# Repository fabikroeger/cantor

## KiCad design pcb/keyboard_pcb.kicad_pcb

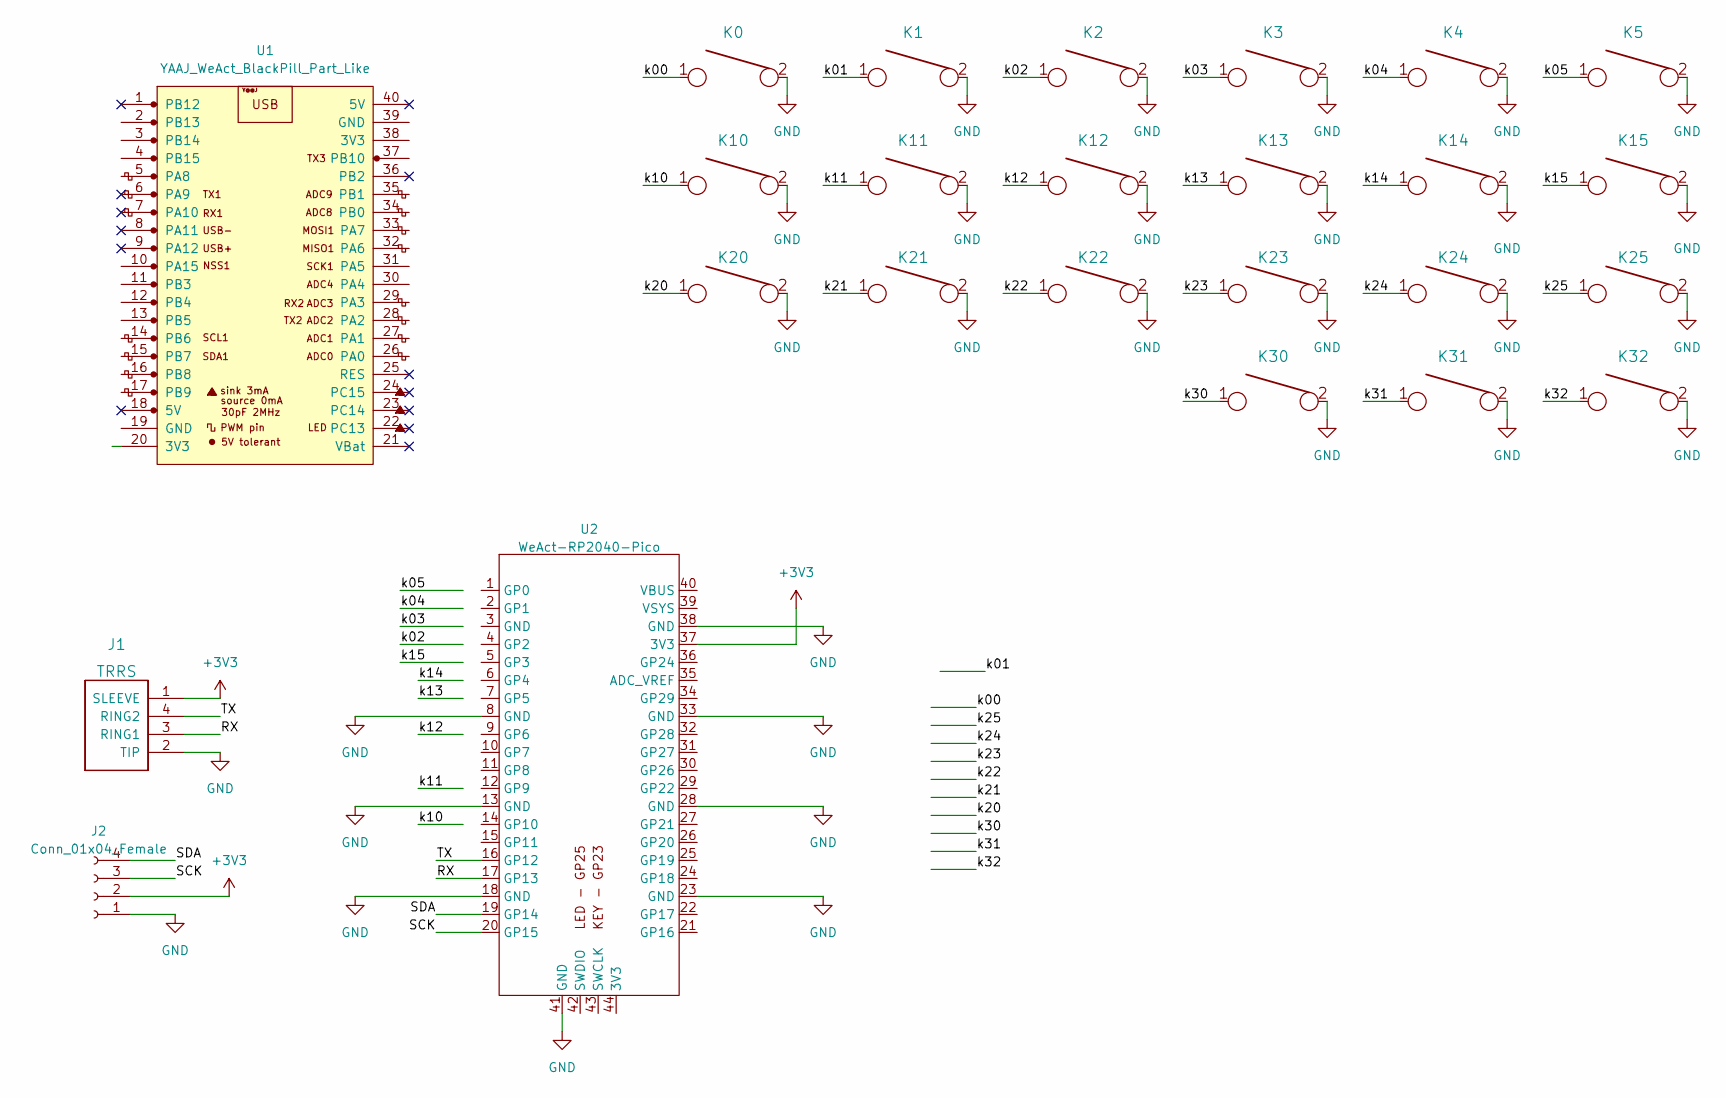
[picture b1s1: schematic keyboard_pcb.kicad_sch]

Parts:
J1: TRRS; TRRS-PJ-320A
J2: Conn_01x04_Female
K0, K1, K2, K3, K4, K5, K10, K11, K12, K13, K14, K15, K20, K21, K22, K23, K24, K25, K30, K31, K32: KEYSW; SW_PG1350_reversible
U1: YAAJ_WeAct_BlackPill_Part_Like; YAAJ_WeAct_BlackPill_2
U2: WeAct-RP2040-Pico

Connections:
+3V3: J1.1 (SLEEVE), J2.2, U2.37 (3V3)
/RX: J1.3 (RING1), U2.17 (GP13)
/SCK: J2.3, U2.20 (GP15)
/SDA: J2.4, U2.19 (GP14)
/TX: J1.4 (RING2), U2.16 (GP12)
/k00: K0.1
/k01: K1.1
/k02: K2.1
/k03: K3.1
/k04: K4.1
/k05: K5.1
/k10: K10.1
/k11: K11.1
/k12: K12.1
/k13: K13.1
/k14: K14.1
/k15: K15.1
/k20: K20.1
/k21: K21.1
/k22: K22.1
/k23: K23.1
/k24: K24.1
/k25: K25.1
/k30: K30.1
/k31: K31.1
/k32: K32.1
GND: J1.2 (TIP), J2.1, K0.2, K1.2, K2.2, K3.2, K4.2, K5.2, K10.2, K11.2, K12.2, K13.2, K14.2, K15.2, K20.2, K21.2, K22.2, K23.2, K24.2, K25.2, K30.2, K31.2, K32.2, U2.8 (GND), U2.13 (GND), U2.18 (GND), U2.23 (GND), U2.28 (GND), U2.33 (GND), U2.38 (GND), U2.41 (GND)

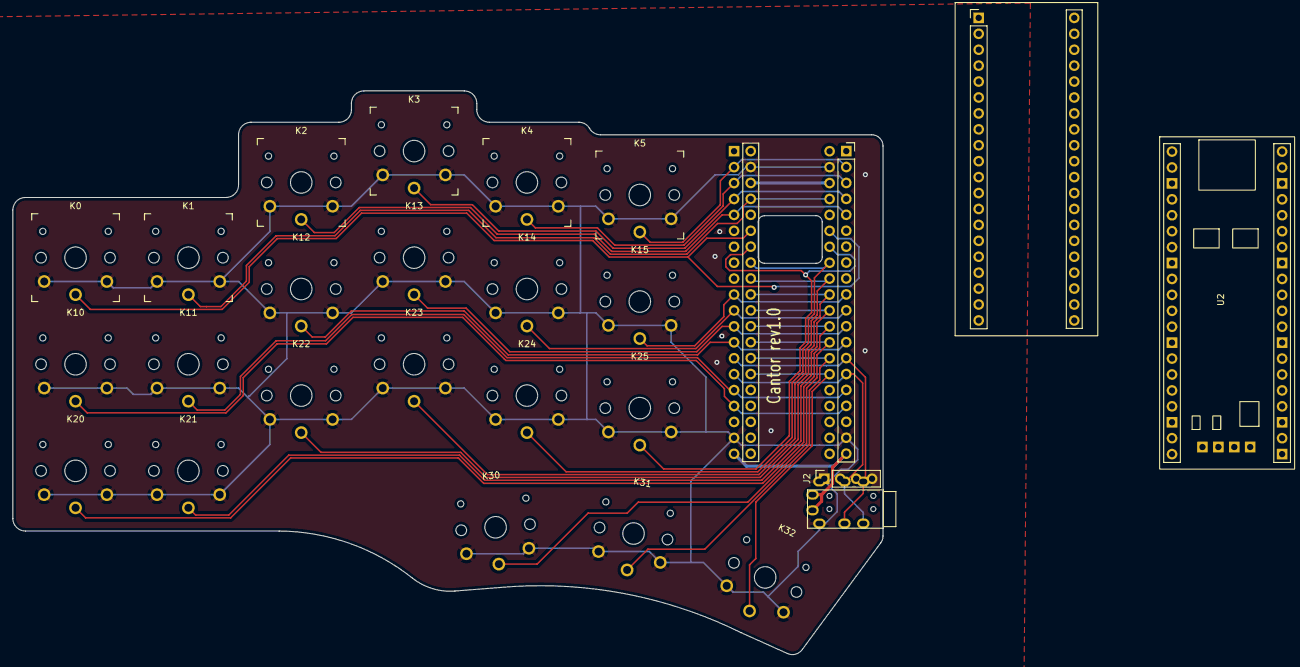
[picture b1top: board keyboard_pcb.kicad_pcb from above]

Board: 2 copper layers, 138.8 x 89.9 mm, 25 parts (0 on the bottom side), 6 nets.

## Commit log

2023-01-25 RP2040 symbol& footprint eingebaut
2023-01-25 WIP: adding RP2040 + oled
